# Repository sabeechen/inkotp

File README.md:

# InkOTP

Firmware that turns an [M5Stack Core Ink](https://docs.m5stack.com/en/core/coreink)
into a small, self-contained TOTP token: an e-ink screen that shows your
one-time codes, with no phone, app or cloud service involved.

It is meant as a backup authenticator for a handful of critical accounts.

> **Status: early.** Version 0.1.0 runs on a Core Ink and its code-generation
> logic passes the RFC test vectors. It has had one user and no outside review.

## What it does

- Shows TOTP codes (SHA-1, SHA-256, SHA-512; 6 to 8 digits; any period), with
  the next code alongside the current one, or three accounts to a screen in
  the optional compact view.
- Keeps time with the Core Ink's battery-backed clock chip, and refuses to show
  codes whenever that clock cannot be trusted.
- Sleeps with a static screen and wakes on a button press.
- Is configured from a phone or computer through a web page the device serves
  on its own short-lived Wi-Fi network.
- Optionally locks behind a PIN made of button presses.
- Optionally clicks its buzzer when a button press registers.

## Design rules

- **Secrets are write-only.** The web UI can add, replace and delete secrets.
  No interface returns one, and the firmware contains no base32 encoder.
- **The radio is normally off.** It is on only during a setup session you start
  from the menu, and for the few seconds of a clock sync.
- **No server dependency.** The clock can always be set from a browser during
  setup; internet time is a convenience.
- **Updates by USB only.** There is no over-the-air update code or partition.

See [SECURITY.md](SECURITY.md) for what this does and does not protect against.

## Controls

| Control | Action |
|---|---|
| Dial up / down | Previous / next account (or page, in compact view), or move in a menu |
| Dial press | Wake; open the menu; select |
| Dial long press | Sleep, from the code screen |
| Top button | Back; sleep from the code screen |
| Side button | Wake; sleep |

Menu: **Codes**, **Sync clock**, **Setup**, **Status**, **Lock now** (when a PIN
is set), **Sleep**.

## First-time setup

1. Wake the device and choose **Setup** from the menu.
2. Scan the first QR code with your phone to join the device's Wi-Fi network.
   Your phone may warn that the network has no internet; stay connected.
   Turn off any VPN on the phone first, or the setup page will not load.
3. Press the dial to show the second QR code and scan it to open the setup page.
4. Press **Set clock from this browser**, then add your accounts. Either
   photograph the QR code a service shows you (or choose a saved image of it),
   or paste the secret key or the whole `otpauth://` link.
5. Optionally save a Wi-Fi network for automatic clock sync, and set a PIN.
   The same page reorders accounts and holds the other settings: compact
   view, button sounds, the idle time before sleep and a line of text for the
   sleep screen.
6. Press the top button on the device to leave setup.

If you cannot scan, turn the dial up or down on either QR code to show the same
details in large type: the network name and password, then the page address
(`192.168.4.1`) and the access code.

To erase the device without the PIN, hold the top button while switching it on
and follow the prompts.

## Installing a release

Each [release](https://github.com/sabeechen/inkotp/releases) carries two
files, built by GitHub Actions from the tagged source. Flash them over USB
with [esptool](https://docs.espressif.com/projects/esptool/) (`pip install
esptool`), or from Chrome or Edge with Espressif's
[browser flasher](https://espressif.github.io/esptool-js/).

A first install, which **erases any accounts and settings on the device**:

```sh
esptool --chip esp32 write-flash 0x0 inkotp-coreink-0.1.0-full.bin
```

An update to a device that already runs InkOTP, which keeps them:

```sh
esptool --chip esp32 write-flash 0x10000 inkotp-coreink-0.1.0-update.bin
```

## Building

Requires [PlatformIO](https://platformio.org/).

```sh
pio run                # build
pio run -t upload      # flash over USB
pio test -e native     # run the host tests
```

On Linux you may need to be in the `dialout` group to flash.

To work on the web UI without a device:

```sh
python3 tools/mock_device.py
```

## Layout

| Path | Contents |
|---|---|
| `lib/otpcore/` | Hashing, HMAC, TOTP and `otpauth://` parsing. No hardware dependencies. |
| `src/` | Firmware: screens, storage, clock, PIN lock, clock sync, setup portal. |
| `web/index.html` | The setup page, embedded in the firmware image. |
| `web/vendor/` | [jsQR](https://github.com/cozmo/jsQR) 1.4.0 (Apache-2.0), which reads QR codes from photos in the browser. |
| `test/` | Host tests for `lib/otpcore`. |
| `tools/` | Constant-table generator, the mock device and the build step that makes the single-file image. |
| `hardware/` | An unbuilt draft of a thinner custom board and a printed case. The firmware does not support it yet; see `hardware/README.md`. |

## Limitations

- QR codes are read from a photo, not a live camera view: browsers only allow
  live camera access over HTTPS, which the device does not serve.
- Export codes from authenticator apps (`otpauth-migration://`) are not
  supported.
- Account names are limited to 32 printable ASCII characters.
- Up to 24 accounts and 6 Wi-Fi networks.
- The setup page is served over plain HTTP, protected by the Wi-Fi network's
  own encryption. See SECURITY.md.

## Licence

InkOTP is released into the public domain under the [Unlicense](UNLICENSE).

The bundled QR decoder in `web/vendor/` is a separate work under the
Apache License 2.0; see `web/vendor/jsqr.LICENSE`. Firmware built from this
repository also links M5Unified and M5GFX (MIT) and the Arduino-ESP32 core.

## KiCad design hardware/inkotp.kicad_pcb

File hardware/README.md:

# InkOTP stick: custom board

A first-draft board for a thinner InkOTP: an ESP32-S3-MINI-1, the same 1.54 inch
e-ink panel as the Core Ink, three thumb switches, a reset switch, USB-C and a
LiPo cell (plugged in or soldered) on a 32 x 54.5 mm, four-layer, 1.0 mm board.

**Status: unreviewed draft.** It passes KiCad's electrical and design rule
checks, but it has not been reviewed by a person, built or tested. Do not order
boards from it without going through the list under "Before ordering".

## Files

| File | What it is |
| --- | --- |
| `inkotp.kicad_pro`, `.kicad_sch`, `.kicad_pcb` | KiCad 9 project, schematic and routed board |
| `inkotp.kicad_sym`, `inkotp.pretty/` | Project symbol (clock) and footprints (USB port, panel connector, inductor, battery pads, module) |
| `bom.csv` | Parts list with suggested part numbers |
| `sourcing.md` | DigiKey order list with quantities for hand assembly, and why each part was chosen |
| `docs/` | Schematic PDF and board renders |
| `gen/` | The Python scripts that generate all of the above |
| `sim/` | An ngspice simulation of the power latch and reset switch, with its findings |
| `case/` | A 3D-printed case generated from the board's layout; unprinted first draft, see `case/README.md` |

## How it is generated

`gen/design.py` lists every part and its connections, and `gen/layout.py` says
where each part sits. Both the schematic and the board come from those two
files, so they cannot drift apart. The schematic connects pins by net label
instead of drawn wires.

    python3 gen/build.py schematic   # rewrite the schematic only
    python3 gen/build.py board       # rewrite the board, UNROUTED
    python3 gen/route.py freerouting.jar 200   # autoroute it (needs Docker)
    python3 gen/bom.py               # rewrite bom.csv
    python3 gen/sync.py              # apply a part change to the ROUTED board
    python3 gen/finish.py U5.1 ...   # connect single pads by hand
    python3 gen/labels.py            # print part names on the silkscreen

`build.py board` and `build.py all` discard the routing. The autorouter
(Freerouting 2.1.0) gives a different result on every run and usually leaves a
few connections open; `gen/route_best.py` repeats it and keeps the best
attempt. The last few are quicker to finish by hand than to chase with more
autorouter runs. The committed board is the best of four attempts, finished
with `gen/finish.py`:

- `finish.py R1.2 TP1.1` added a via beside a ground pad and a 3.3 V test pad
  that the pours did not reach;
- its `bridge()` function added two short links on the back face at x = 24 to
  25 mm in the bottom strip, where an inner-layer track had cut the 3.3 V
  plane in two and left the regulator's output on the wrong side.

The USB port's escape routing and the ground vias under the module are placed
by `layout.py` before routing.

### Changing a part without rerouting

When five parts were swapped for ones DigiKey stocks, the board was not
rerouted from scratch. `gen/sync.py` reads `design.py` and updates the routed
board in place: it swaps footprints where they differ, reassigns pad nets, and
removes only the tracks that ran to pads which moved or changed net. That left
six open connections around the clock chip, whose pin order had changed.
`route.py` can finish a partly routed board, but took twelve minutes and left
three open, so they were finished with `finish.py`, which routes a named pad to
the nearest copper of its net:

    python3 gen/finish.py U5.2 U5.3 U5.8 R14.1 U5.1 U5.6 J3.MP

The order matters: each route becomes an obstacle for the next. One leftover
via and a stub of track on the clock's SCL line were then removed by hand.

The reset switch was added the same way. `sync.py` places a new part if
`layout.py` gives it a fixed position, and these connected it and moved the up
switch to the boot pin:

    python3 gen/finish.py U1.4:14.5:0.1 TP4.1:11:0.1 SW4.1:9:0.1

The numbers after a pad are how far to search, in millimetres, and the grid.

## Reset and recovery

SW4, below the three thumb switches on the same edge, pulls the module's
enable pin low. It is the same part as the thumb switches and is meant to sit
behind a pinhole in the case, or a recessed cut-out, so that a thumb cannot
press it by accident.

- **Tap:** resets the processor. The power latch rides through (C3 holds Q2
  on for about a second).
- **Hold for two seconds or more, on battery:** C3 discharges, the latch lets
  go and the device switches off, even if the firmware has hung with its
  hold line high. On USB power the device stays on.
- **Hold Up, tap reset:** the up switch is on IO0, the boot-mode pin, so the
  chip starts its built-in USB loader. That loader is in ROM and cannot be
  erased, so a board with broken firmware can always be reflashed. Holding
  Up while switching on does the same; on battery the device switches off
  again when the switches are released.

None of this has been tried on hardware. Firmware should still enable the
chip's watchdog, which recovers from most hangs without anyone pressing
anything.

## Battery

The cell lies below the board's bottom edge and connects in one of two ways,
which are the same two nets:

- **J4**, a JST SH side-entry socket (SM02B-SRSS-TB, 2.9 mm tall) below the
  USB port, mouth out of the bottom edge. `+` on the silkscreen marks its
  positive contact. It sits 0.3 mm from the USB port's shell tab, which is
  why `inkotp.kicad_dru` lets those two courtyards overlap, and its footprint
  is KiCad's with one corner of the outline removed.
- **J2**, two solder pads in the opposite bottom corner.

The board has no protection against a reversed cell and none of its own
against running the cell flat. What there is:

- When off, Q1 disconnects everything except the clock's backup pin and the
  charger's leakage, a few microamps in all by the datasheets (not measured),
  which a 200 mAh cell can supply for years.
- When on, firmware can read the cell through IO1 and switch off by letting
  go of the hold line. It does not do this yet for this board; about 3.3 V is
  a sensible threshold.
- If firmware hangs with the hold line high, nothing on the board stops the
  drain. The cell's own protection board is then the only cut-off, usually
  near 2.5 V, which is why `sourcing.md` asks for a protected cell. The
  watchdog and the reset switch are the defences against the hang itself.
- The charger (MCP73832) trickle-charges a deeply discharged cell before
  charging at full current.

## Labels

`gen/labels.py` prints each part's value or name beside it in silkscreen, and
the function of each switch, test pad and the battery's positive pad. Text is
0.8 mm tall with 0.15 mm lines and stays 0.15 mm from pads. Run it again after
any change to the parts; it replaces its own labels.

- Identical parts that sit together share one label with a count, such as
  `1u 25V x5`.
- Six parts had no room for their name and carry their reference instead:
  Q1, Q2, Q3, C11, C16 and R2. A key printed in the open area below the panel
  connector says what each is, and `bom.csv` lists every reference.
- Three parts have no label at all: Q4 (AO3400A), the three-pin part between
  the inductor and the board edge, which the key lists; L1 (47uH), the
  inductor; and R12 (1k), the small part between the battery socket and the
  one labelled `100n`.
- The transistor marks, the key, the socket's `+` and one `5.1k` are at
  positions set by hand in `labels.py`, not found by the script.
- The top row beside the clock chip is tight: its three small parts are, from
  the up switch towards the module, 10k, 10k and 100n. `10k x2` is printed at
  the switch end.
- `PANEL` marks the connector, with `1` and `24` at its end contacts. The
  battery's negative pad is the unmarked one next to `BAT+`.

## Fabrication limits

The board's rules in `inkotp.kicad_pro` (written by `gen/libs.py`) and
`inkotp.kicad_dru` are JLCPCB's published limits for multilayer boards, read in
November 2026, and the board passes KiCad's rule check against them. Order it
as four layers, 1.0 mm thick, with tented vias.

- Tracks and gaps are 0.127 mm; vias are 0.45 mm with a 0.2 mm hole, the
  smallest JLCPCB makes without a surcharge. PCBWay's standard limits ask for
  a wider ring around each via (0.15 mm against this board's 0.125 mm).
- Copper stays 0.2 mm from every routed edge. To get there the USB port's
  pads are 0.05 mm shorter than GCT draws them, and five tracks and a via
  beside the panel slot and the right edge were moved by hand.
- Label text is 0.8 mm tall. JLCPCB asks for 1.0 mm, which does not fit on
  the back face; expect the labels to print but not crisply.
- The slot and the USB notch are drawn with square inside corners. A router
  leaves them rounded, by a radius JLCPCB does not publish; check that the
  USB port's body clears the notch corners.
- Thickness is held to 10% and the outline to 0.2 mm (0.1 mm on request).

## Layout

Coordinates in `layout.py` are seen from the front (screen side). The glass
covers the top 37.3 mm, so everything behind it is on the back face. The
panel's tail passes through the slot below the glass and folds up the back
into its connector. Below the slot there is no glass; the chips for charging
and power sit on the back there, and their resistors and capacitors sit on the
front with hand-solder pads.

Inner layer 1 is ground and inner layer 2 is 3.3 V.

## Before ordering

- **Edge switches.** Four Panasonic EVQP7J01P side-push switches use KiCad's
  stock footprint. Panasonic does not say where the board edge should sit; it
  is set 1.5 mm from the switch centre, leaving about 0.6 mm of plunger
  overhang. The switches have no mounting tabs, so the case's button cap must
  bottom out on the case and not on the switches.
- **3.3 V plane.** The regulator's output reaches the rest of the board through
  the two hand-added links described above. Rerouting the inner-layer track
  that splits the plane would be better.
- **USB port footprint.** Drawn from GCT's USB4505 drawing, which gives the
  pattern for a 0.8 mm board; this board is 1.0 mm.
- **Panel connector.** Hirose FH34SRJ-24S-0.5SH(50), which touches both faces
  of the tail. Its footprint is drawn from Hirose's catalogue and has not been
  checked against a part. The pad order follows Good Display's photos and
  drawing of the GDEY0154D67 with the tail folded behind the board. The signal
  pads are where the earlier TE connector's were, so how far the tail reaches
  into this connector is an estimate, good to about 0.5 mm; the fold has that
  much slack, but confirm the tail reaches and seats.
- **Clock.** RV-3032-C7 in place of the RV-3028-C7. Its clock output pin is
  left open and is on by default; firmware should turn it off, and must enable
  the backup switchover. The routing around it was done by `finish.py`.
- **Buzzer.** Same Sky CPT-9019A-SMT-TR on the Murata footprint, which has the
  same pads. Its datasheet draws the pads turned a quarter turn from the body
  views; check which edges the terminals are on before soldering.
- **Panel drive circuit.** Copied from the panel datasheet's reference circuit.
  The datasheet's two pin tables disagree about pin 4, so C22 is an unfitted
  footprint there. The inductor (Wurth 74404032470) saturates at 0.41 A against
  the 0.5 A the datasheet asks for; no 47 uH part of this size reaches 0.5 A.
  Its footprint is drawn from Wurth's datasheet.
- **Antenna.** Copper is kept clear only directly under and beside the
  antenna, far less than Espressif recommends. Expect reduced Wi-Fi range.
- **Routing quality.** Autorouted. The boost stage, the USB data pair and the
  battery and 3.3 V paths have not been laid out with any care.
- **Power latch.** Simulated in `sim/` but not built. The simulation found
  that the first draft (a Schottky pair for D1, 1 M for R4) could switch
  itself on when warm, so D1 is now a BAV70 and R4 is 100 k. The models are
  generic; see `sim/README.md` for how far to trust them.
- **Reset switch.** Untested, like the power latch it works with. Its two
  hold times depend on C3 and R6; see "Reset and recovery".
- **Battery.** The socket's position against the USB port, and which way
  round the lead goes, have not been checked on a part.
- **Labels.** Placed by script and checked only against KiCad's silkscreen
  rules and a render. The text is smaller than JLCPCB's stated minimum; see
  "Fabrication limits". Compare them with `bom.csv` before trusting one.
- **Firmware.** The pin map differs from the Core Ink, and the board has no
  support in the firmware yet. The up switch is on IO0. Firmware must raise
  the hold line as early as it can, because the board stays on only while
  select is held until then, and should wait 0.3 s after power-on before
  reading the battery.

## Soldering

The back face needs hot air or a hotplate for the module, the clock chip and
the USB port. The front face carries only two-terminal passives and
can be done with an iron afterwards.

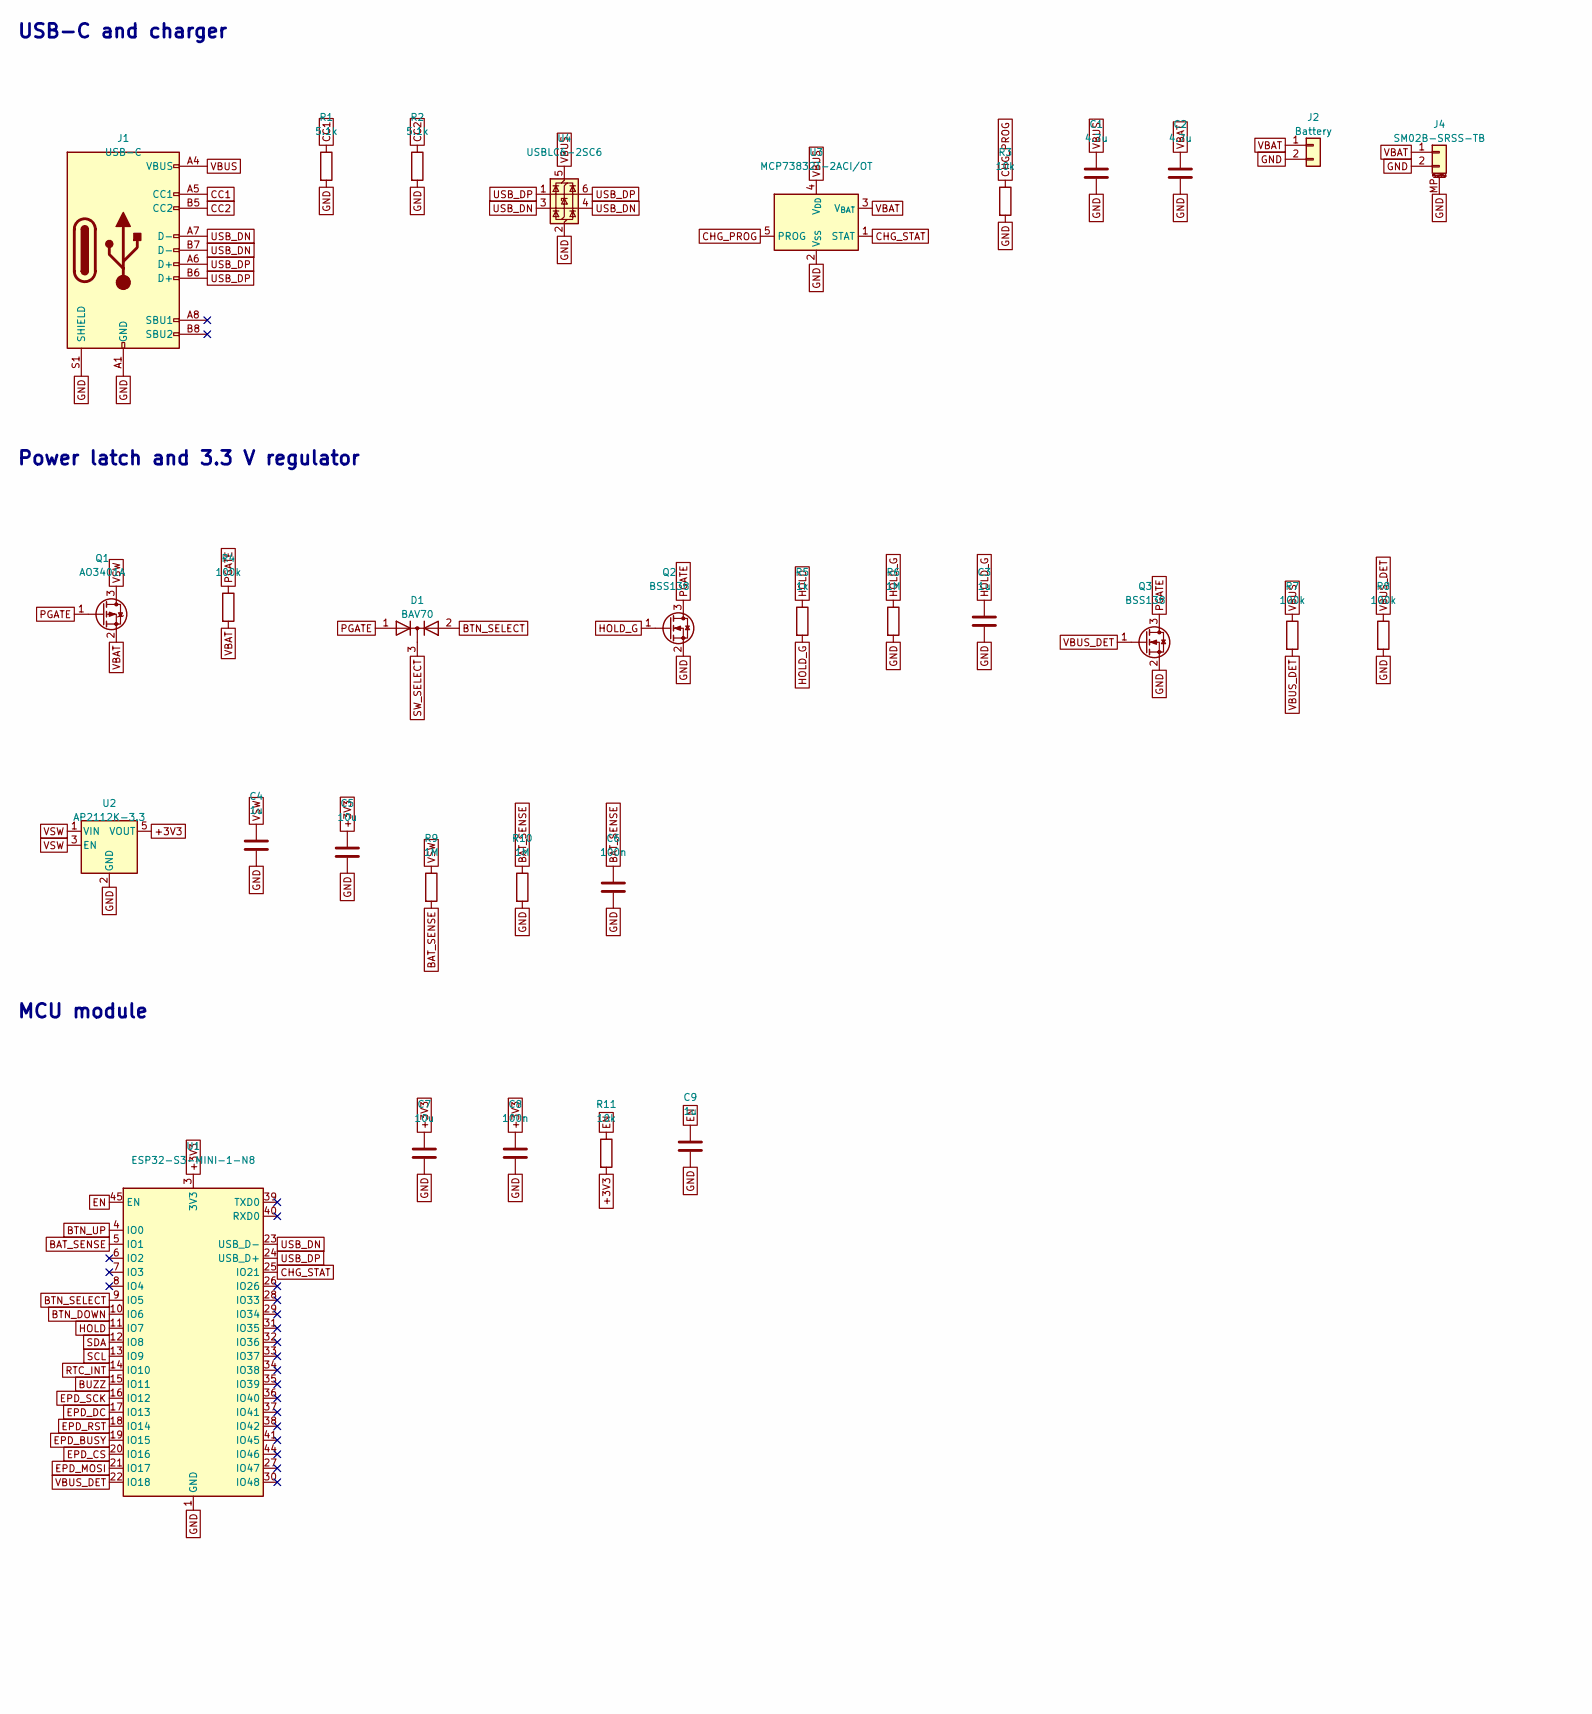
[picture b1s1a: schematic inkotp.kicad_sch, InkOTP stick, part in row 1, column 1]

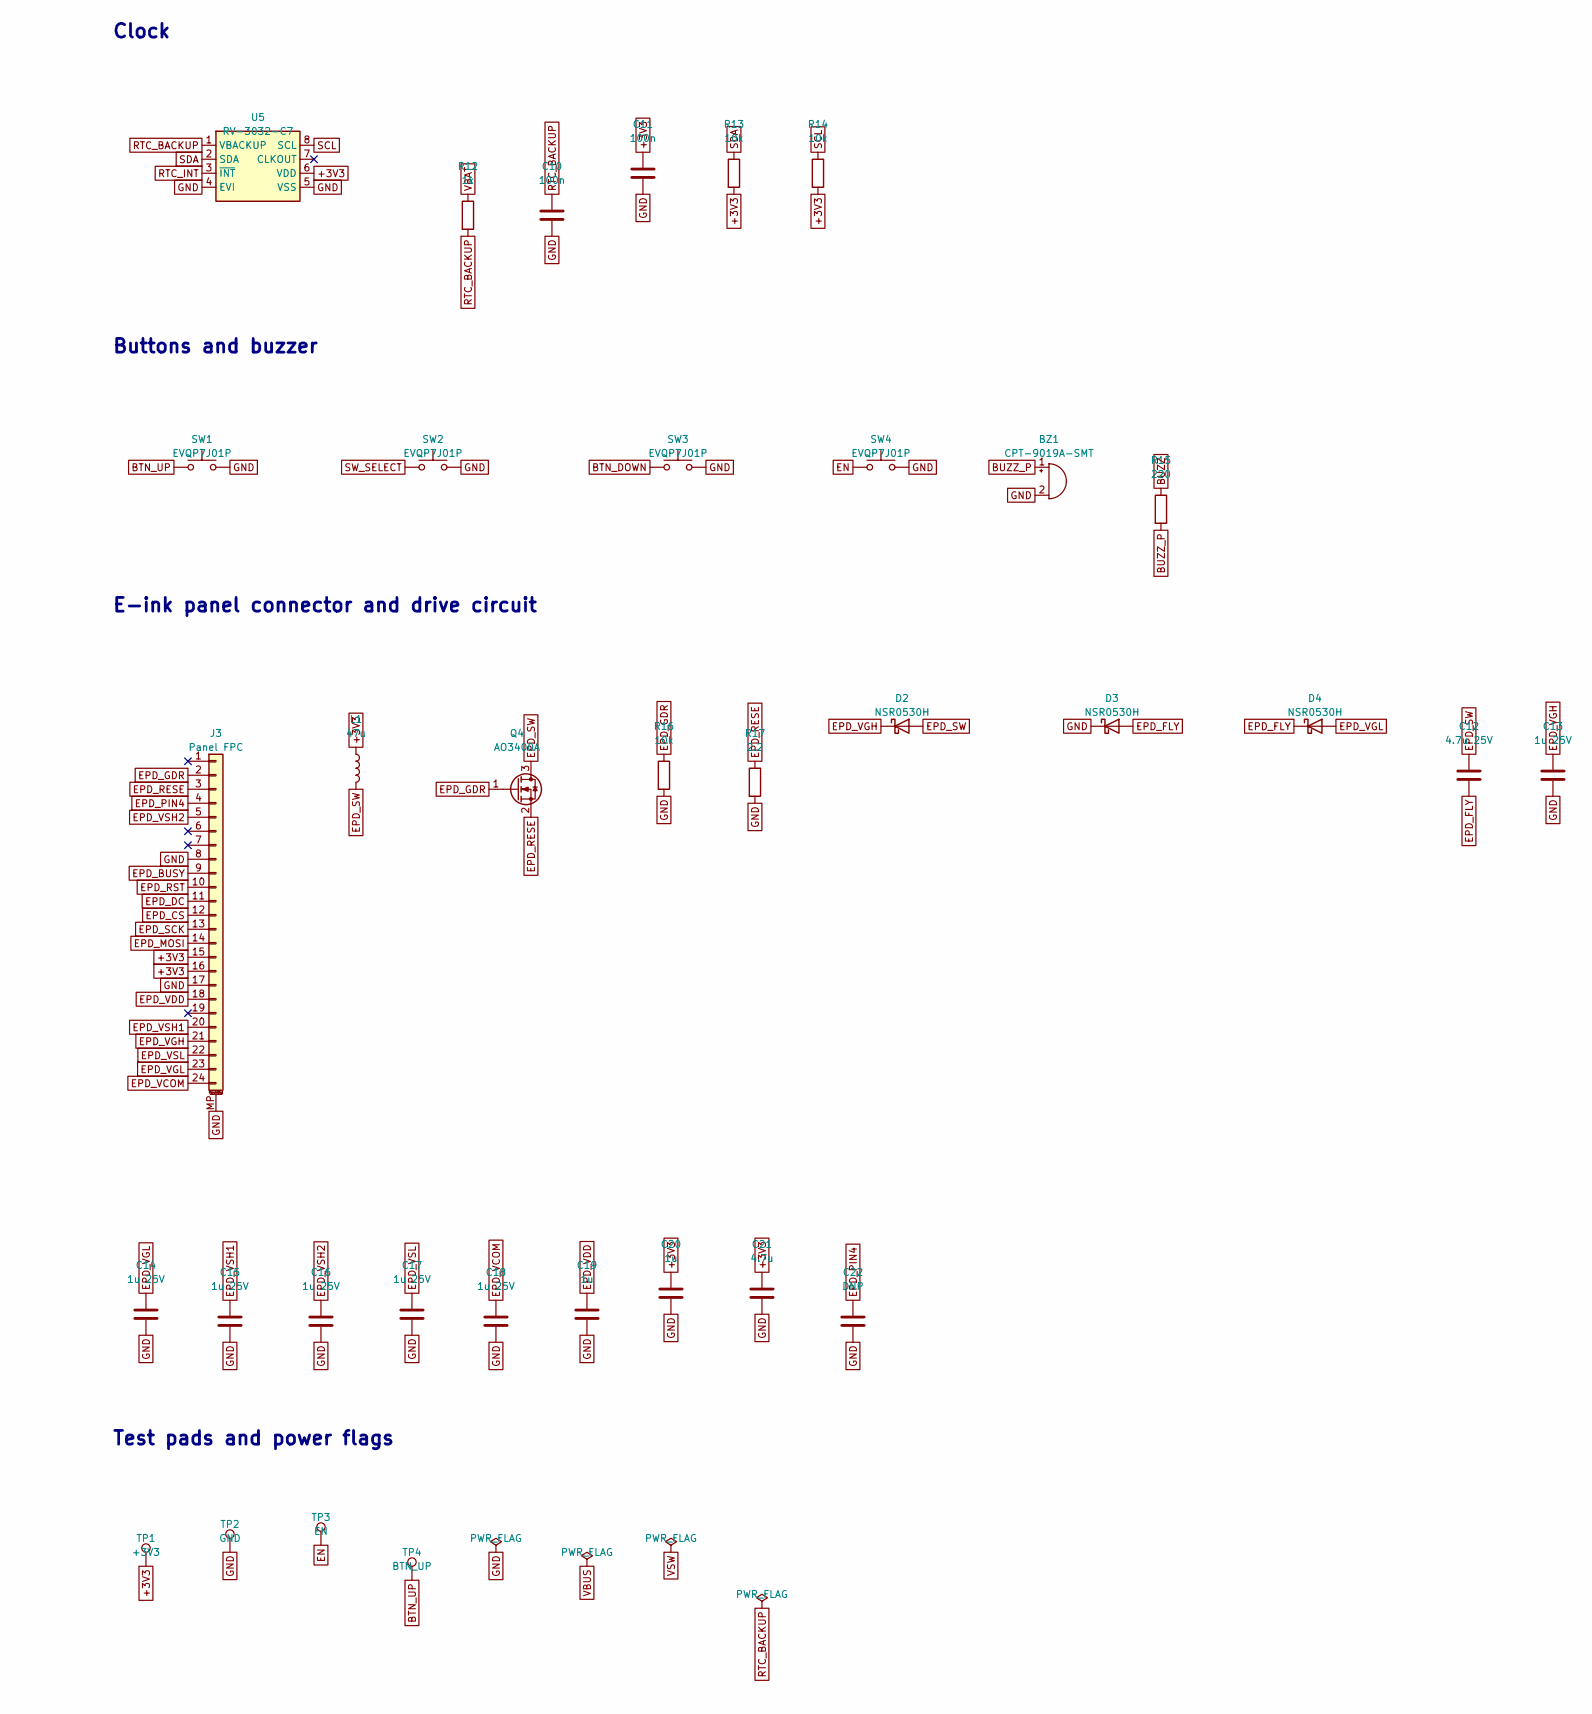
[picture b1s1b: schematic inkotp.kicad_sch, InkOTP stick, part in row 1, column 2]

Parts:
BZ1: CPT-9019A-SMT; Buzzer_Murata_PKMCS0909E
C1, C2: 4.7u; C_0603_1608Metric_Pad1.08x0.95mm_HandSolder
C3, C4: 1u; C_0402_1005Metric_Pad0.74x0.62mm_HandSolder
C5: 10u; C_0603_1608Metric_Pad1.08x0.95mm_HandSolder
C6: 100n; C_0402_1005Metric_Pad0.74x0.62mm_HandSolder
C7: 10u; C_0603_1608Metric
C8, C10, C11: 100n; C_0402_1005Metric
C9, C19, C20: 1u; C_0402_1005Metric
C12: 4.7u 25V; C_0603_1608Metric
C13, C14, C15, C16, C17, C18: 1u 25V; C_0603_1608Metric
C21: 4.7u; C_0603_1608Metric
C22: DNP; C_0603_1608Metric
D1: BAV70; SOT-23
D2, D3, D4: NSR0530H; D_SOD-323
J1: USB-C; USB_C_MidMount
J2: Battery; BatteryPads
J3: Panel FPC; Hirose_FH34SRJ-24S-0.5SH
J4: SM02B-SRSS-TB; JST_SH_SM02B-SRSS-TB
L1: 47u; L_Wuerth_WE-LQS-3015
Q1: AO3401A; SOT-23
Q2, Q3: BSS138; SOT-23
Q4: AO3400A; SOT-23
R1, R2: 5.1k; R_0402_1005Metric
R3: 10k; R_0402_1005Metric_Pad0.72x0.64mm_HandSolder
R4, R7, R8: 100k; R_0402_1005Metric_Pad0.72x0.64mm_HandSolder
R5: 1k; R_0402_1005Metric_Pad0.72x0.64mm_HandSolder
R6, R9, R10: 1M; R_0402_1005Metric_Pad0.72x0.64mm_HandSolder
R11, R13, R14, R16: 10k; R_0402_1005Metric
R12: 1k; R_0402_1005Metric
R15: 220; R_0402_1005Metric
R17: 2.2; R_0402_1005Metric
SW1, SW2, SW3, SW4: EVQP7J01P; SW_SPST_EVQP7A
TP1: +3V3; TestPoint_Pad_D1.0mm
TP2: GND; TestPoint_Pad_D1.0mm
TP3: EN; TestPoint_Pad_D1.0mm
TP4: BTN_UP; TestPoint_Pad_D1.0mm
U1: ESP32-S3-MINI-1-N8; ESP32-S3-MINI-1
U2: AP2112K-3.3; SOT-23-5
U3: MCP73832T-2ACI/OT; SOT-23-5
U4: USBLC6-2SC6; SOT-23-6
U5: RV-3032-C7; MicroCrystal_C7_SON-8_1.5x3.2mm_P0.9mm

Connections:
+3V3: C5.1, C7.1, C8.1, C11.1, C20.1, C21.1, J3.15, J3.16, L1.1, R11.2, R13.2, R14.2, TP1.1, U1.3 (3V3), U2.5 (VOUT), U5.6 (VDD)
BAT_SENSE: C6.1, R9.2, R10.1, U1.5 (IO1)
BTN_DOWN: SW3.1, U1.10 (IO6)
BTN_SELECT: D1.2 (A), U1.9 (IO5)
BTN_UP: SW1.1, TP4.1, U1.4 (IO0)
BUZZ: R15.1, U1.15 (IO11)
BUZZ_P: BZ1.1 (+), R15.2
CC1: J1.A5 (CC1), R1.1
CC2: J1.B5 (CC2), R2.1
CHG_PROG: R3.1, U3.5 (PROG)
CHG_STAT: U1.25 (IO21), U3.1 (STAT)
EN: C9.1, R11.1, SW4.1, TP3.1, U1.45 (EN)
EPD_BUSY: J3.9, U1.19 (IO15)
EPD_CS: J3.12, U1.20 (IO16)
EPD_DC: J3.11, U1.17 (IO13)
EPD_FLY: C12.2, D3.2 (A), D4.1 (K)
EPD_GDR: J3.2, Q4.1 (G), R16.1
EPD_MOSI: J3.14, U1.21 (IO17)
EPD_PIN4: C22.1, J3.4
EPD_RESE: J3.3, Q4.2 (S), R17.1
EPD_RST: J3.10, U1.18 (IO14)
EPD_SCK: J3.13, U1.16 (IO12)
EPD_SW: C12.1, D2.2 (A), L1.2, Q4.3 (D)
EPD_VCOM: C18.1, J3.24
EPD_VDD: C19.1, J3.18
EPD_VGH: C13.1, D2.1 (K), J3.21
EPD_VGL: C14.1, D4.2 (A), J3.23
EPD_VSH1: C15.1, J3.20
EPD_VSH2: C16.1, J3.5
EPD_VSL: C17.1, J3.22
GND: BZ1.2 (-), C1.2, C2.2, C3.2, C4.2, C5.2, C6.2, C7.2, C8.2, C9.2, C10.2, C11.2, C13.2, C14.2, C15.2, C16.2, C17.2, C18.2, C19.2, C20.2, C21.2, C22.2, D3.1 (K), J1.A1 (GND), J1.A12 (GND), J1.B1 (GND), J1.B12 (GND), J1.S1 (SHIELD), J2.2, J3.8, J3.17, J3.MP (MountPin), J4.2, J4.MP (MountPin), Q2.2 (S), Q3.2 (S), R1.2, R2.2, R3.2, R6.2, R8.2, R10.2, R16.2, R17.2, SW1.2, SW2.2, SW3.2, SW4.2, TP2.1, U1.1 (GND), U1.2 (GND), U1.42 (GND), U1.43 (GND), U1.46 (GND), U1.47 (GND), U1.48 (GND), U1.49 (GND), U1.50 (GND), U1.51 (GND), U1.52 (GND), U1.53 (GND), U1.54 (GND), U1.55 (GND), U1.56 (GND), U1.57 (GND), U1.58 (GND), U1.59 (GND), U1.60 (GND), U1.61 (GND), U1.62 (GND), U1.63 (GND), U1.64 (GND), U1.65 (GND), U2.2 (GND), U3.2 (V_{SS}), U4.2 (GND), U5.4 (EVI), U5.5 (VSS)
HOLD: R5.1, U1.11 (IO7)
HOLD_G: C3.1, Q2.1 (G), R5.2, R6.1
PGATE: D1.1 (A), Q1.1 (G), Q2.3 (D), Q3.3 (D), R4.1
RTC_BACKUP: C10.1, R12.2, U5.1 (VBACKUP)
RTC_INT: U1.14 (IO10), U5.3 (~INT)
SCL: R14.1, U1.13 (IO9), U5.8 (SCL)
SDA: R13.1, U1.12 (IO8), U5.2 (SDA)
SW_SELECT: D1.3 (K), SW2.1
USB_DN: J1.A7 (D-), J1.B7 (D-), U1.23 (USB_D-), U4.3 (I/O2), U4.4 (I/O2)
USB_DP: J1.A6 (D+), J1.B6 (D+), U1.24 (USB_D+), U4.1 (I/O1), U4.6 (I/O1)
VBAT: C2.1, J2.1, J4.1, Q1.2 (S), R4.2, R12.1, U3.3 (V_{BAT})
VBUS: C1.1, J1.A4 (VBUS), J1.A9 (VBUS), J1.B4 (VBUS), J1.B9 (VBUS), R7.1, U3.4 (V_{DD}), U4.5 (VBUS)
VBUS_DET: Q3.1 (G), R7.2, R8.1, U1.22 (IO18)
VSW: C4.1, Q1.3 (D), R9.1, U2.1 (VIN), U2.3 (EN)

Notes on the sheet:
USB-C and charger
Power latch and 3.3 V regulator
MCU module
Clock
Buttons and buzzer
E-ink panel connector and drive circuit
Test pads and power flags

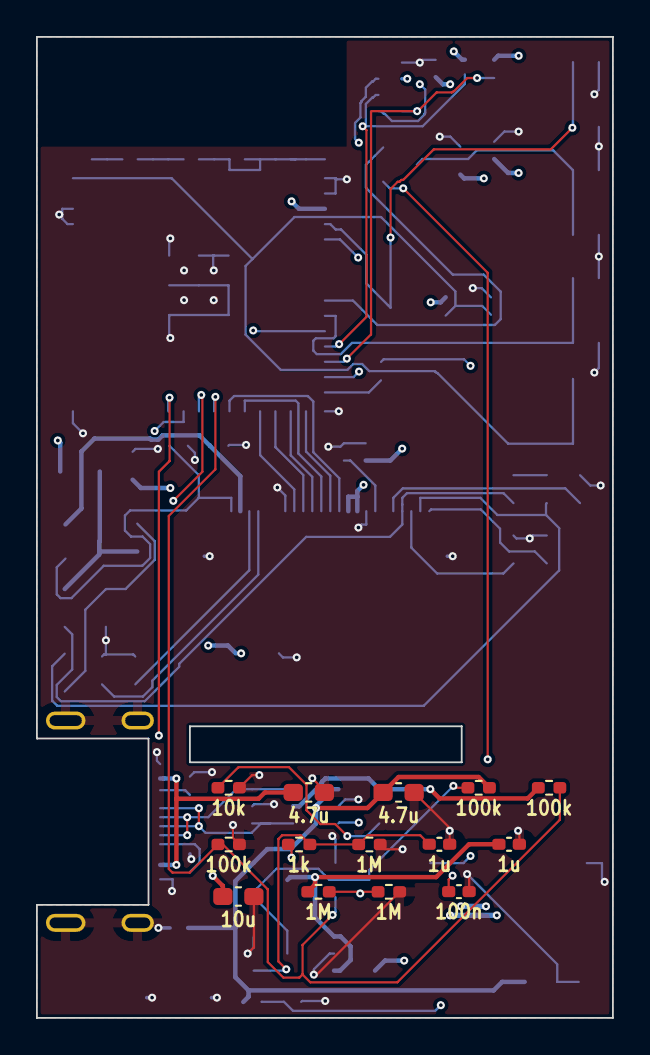
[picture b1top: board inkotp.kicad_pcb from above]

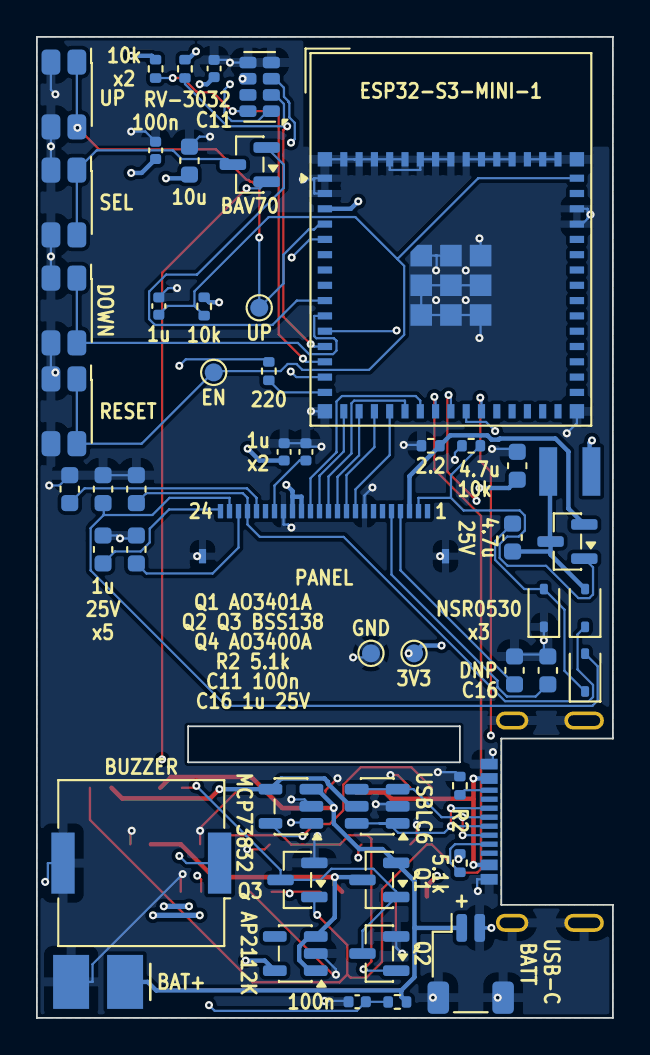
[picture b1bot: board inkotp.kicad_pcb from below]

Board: 4 copper layers, 32.0 x 54.5 mm, 66 parts (52 on the bottom side), 45 nets.

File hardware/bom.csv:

References,Quantity,Value,Footprint,Manufacturer,Part number,Note
BZ1,1,CPT-9019A-SMT,Buzzer_Murata_PKMCS0909E,Same Sky,CPT-9019A-SMT-TR,"piezo sounder, 9 x 9 x 1.9 mm"
C1 C2 C21,3,4.7u,C_0603_1608Metric,,,"ceramic capacitor, X5R or X7R"
C3 C4 C9 C19 C20,5,1u,C_0402_1005Metric,,,"ceramic capacitor, X5R or X7R"
C5 C7,2,10u,C_0603_1608Metric,,,"ceramic capacitor, X5R or X7R"
C6 C8 C10 C11,4,100n,C_0402_1005Metric,,,"ceramic capacitor, X5R or X7R"
C12,1,4.7u 25V,C_0603_1608Metric,,,"ceramic capacitor, X5R or X7R, 25 V or higher"
C13 C14 C15 C16 C17 C18,6,1u 25V,C_0603_1608Metric,,,"ceramic capacitor, X5R or X7R, 25 V or higher"
C22,1,DNP,C_0603_1608Metric,,,not fitted
D1,1,BAV70,SOT-23,Nexperia,"BAV70,215","dual switching diode, common cathode; not a Schottky, which leaks too much"
D2 D3 D4,3,NSR0530H,D_SOD-323,onsemi,NSR0530HT1G,30 V 0.5 A Schottky
J1,1,USB-C,USB_C_MidMount,GCT,USB4505-03-0-A,"mid-mount, 1.0 mm offset"
J2,1,Battery,BatteryPads,,,"solder pads only, no part"
J3,1,Panel FPC,Hirose_FH34SRJ-24S-0.5SH,Hirose,FH34SRJ-24S-0.5SH(50),"24 pin 0.5 mm, contacts on both faces, 1.0 mm tall"
J4,1,SM02B-SRSS-TB,JST_SH_SM02B-SRSS-TB,JST,SM02B-SRSS-TB,"battery socket, JST SH 2 pin side entry, 2.9 mm tall; optional, the pads at J2 do the same job"
L1,1,47u,L_Wuerth_WE-LQS-3015,Wurth,74404032470,"47 uH, 3 x 3 x 1.5 mm, 0.41 A saturation; the panel datasheet asks for 0.5 A"
Q1,1,AO3401A,SOT-23,Alpha & Omega,AO3401A,"P-channel, battery switch"
Q2 Q3,2,BSS138,SOT-23,onsemi,BSS138,"N-channel, logic level"
Q4,1,AO3400A,SOT-23,Alpha & Omega,AO3400A,"N-channel 30 V, panel boost switch"
R1 R2,2,5.1k,R_0402_1005Metric,,,"resistor, 1 %"
R3 R11 R13 R14 R16,5,10k,R_0402_1005Metric,,,"resistor, 1 %"
R4 R7 R8,3,100k,R_0402_1005Metric,,,"resistor, 1 %"
R5 R12,2,1k,R_0402_1005Metric,,,"resistor, 1 %"
R6 R9 R10,3,1M,R_0402_1005Metric,,,"resistor, 1 %"
R15,1,220,R_0402_1005Metric,,,"resistor, 1 %"
R17,1,2.2,R_0402_1005Metric,,,"resistor, 1 %"
SW1 SW2 SW3 SW4,4,EVQP7J01P,SW_SPST_EVQP7A,Panasonic,EVQP7J01P,"side-push tactile switch, 1.6 N, 1.35 mm tall"
U1,1,ESP32-S3-MINI-1-N8,ESP32-S3-MINI-1,Espressif,ESP32-S3-MINI-1-N8,"PCB antenna version, 8 MB flash"
U2,1,AP2112K-3.3,SOT-23-5,Diodes Inc.,AP2112K-3.3TRG1,600 mA LDO with enable
U3,1,MCP73832T-2ACI/OT,SOT-23-5,Microchip,MCP73832T-2ACI/OT,"4.2 V charger, open-drain status"
U4,1,USBLC6-2SC6,SOT-23-6,STMicroelectronics,USBLC6-2SC6,USB ESD protection
U5,1,RV-3032-C7,MicroCrystal_C7_SON-8_1.5x3.2mm_P0.9mm,Micro Crystal,RV-3032-C7-32.768KHZ-2.5PPM-TA-QC,temperature-compensated clock
Panel,1,,off board,Good Display,GDEY0154D67,1.54 in 200 x 200 e-ink panel
Battery,1,,off board,,"LiPo 3.7 V, about 3 x 26 x 30 mm, with protection circuit","for example a 302530 cell, 200 to 250 mAh"
PCB,1,,off board,,"4 layer, 1.0 mm thick, 32 x 54.5 mm","0.127 mm track and gap, 0.2 mm drill"

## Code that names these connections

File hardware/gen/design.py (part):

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# folds behind the board, which reverses its pin order as the connector sees
# it. The Hirose connector numbers its contacts from the other end to most, so
# the two reversals cancel: connector pad n carries panel pin n.
PANEL = {2: "EPD_GDR", 3: "EPD_RESE", 4: "EPD_PIN4", 5: "EPD_VSH2", 8: "GND", 9: "EPD_BUSY",
         10: "EPD_RST", 11: "EPD_DC", 12: "EPD_CS", 13: "EPD_SCK", 14: "EPD_MOSI", 15: "+3V3",
         16: "+3V3", 17: "GND", 18: "EPD_VDD", 20: "EPD_VSH1", 21: "EPD_VGH", 22: "EPD_VSL",
         23: "EPD_VGL", 24: "EPD_VCOM"}
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cap("C21", "4.7u", "+3V3", "GND", "epd", C0603)
# The datasheet's two pin tables disagree about pin 4; leave this unfitted
# unless the panel turns out to need it.
cap("C22", "DNP", "EPD_PIN4", "GND", "epd", C0603)

# Parts on the front face are soldered with an iron, so they get longer pads.
FRONT = ["R3", "C1", "C2", "R4", "R7", "R8", "R5", "R6", "C3", "C4", "C5", "R9", "R10", "C6"]
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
